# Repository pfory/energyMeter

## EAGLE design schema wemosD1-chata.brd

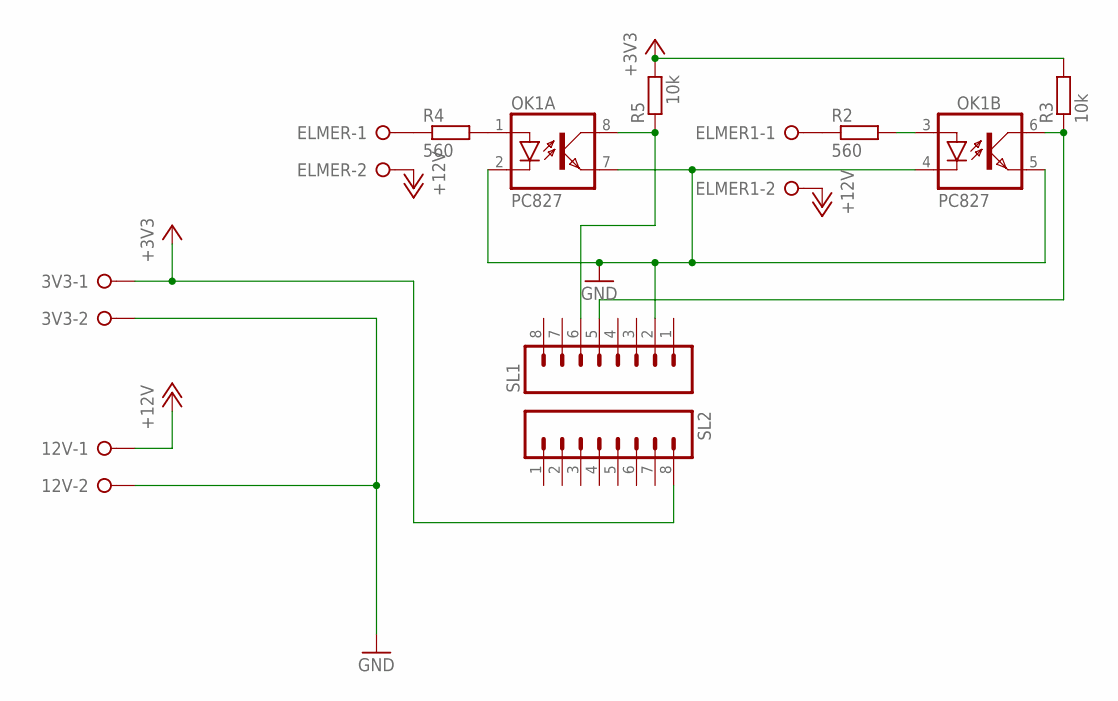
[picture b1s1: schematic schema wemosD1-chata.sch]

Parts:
3V3, 12V: W237-02P; W237-132
ELMER, ELMER1: W237-02P; W237-132
OK1: PC827; DIL08
R2, R4: 560; 0204/7
R3, R5: 10k; 0204/7
SL1, SL2: M08; 08P

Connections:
+3V3: 3V3.1, R3.2, R5.2, SL2.8
+12V: 12V.1, ELMER.2, ELMER1.2
GND: 3V3.2, 12V.2, OK1.2 (C), OK1.4 (C), OK1.5 (EMIT), OK1.7 (EMIT), SL1.2
unnamed: OK1.1 (A), R4.2
unnamed: ELMER1.1, R2.1
unnamed: OK1.3 (A), R2.2
unnamed: OK1.8 (COL), R5.1, SL1.6
unnamed: ELMER.1, R4.1
unnamed: OK1.6 (COL), R3.1, SL1.5

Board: 2 copper layers, 11 parts (0 on the bottom side), 9 nets, no tracks yet.

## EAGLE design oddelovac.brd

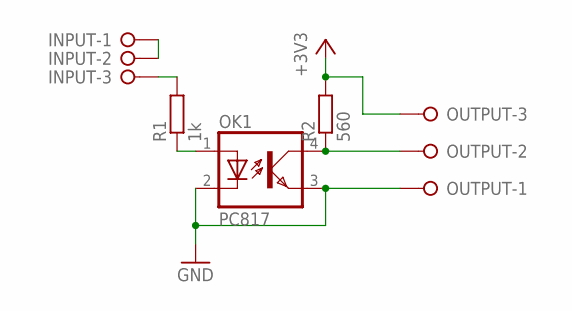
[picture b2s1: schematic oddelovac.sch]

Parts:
INPUT: W237-3E
OK1: PC817; DIL04
OUTPUT: W237-3E
R1: 1k; 0207/7
R2: 560; 0207/7

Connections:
+3V3: OUTPUT.3, R2.2
GND: OK1.2 (C), OK1.3 (EMIT), OUTPUT.1
unnamed: INPUT.3, R1.2
unnamed: OK1.1 (A), R1.1
unnamed: OK1.4 (COL), OUTPUT.2, R2.1
unnamed: INPUT.1, INPUT.2

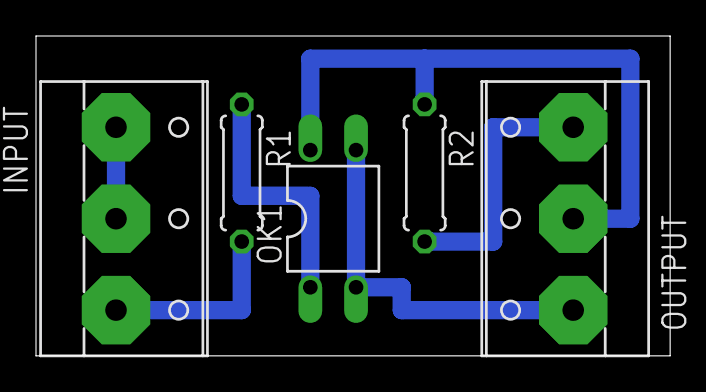
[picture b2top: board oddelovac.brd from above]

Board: 2 copper layers, 35.2 x 17.8 mm, 5 parts (0 on the bottom side), 6 nets.

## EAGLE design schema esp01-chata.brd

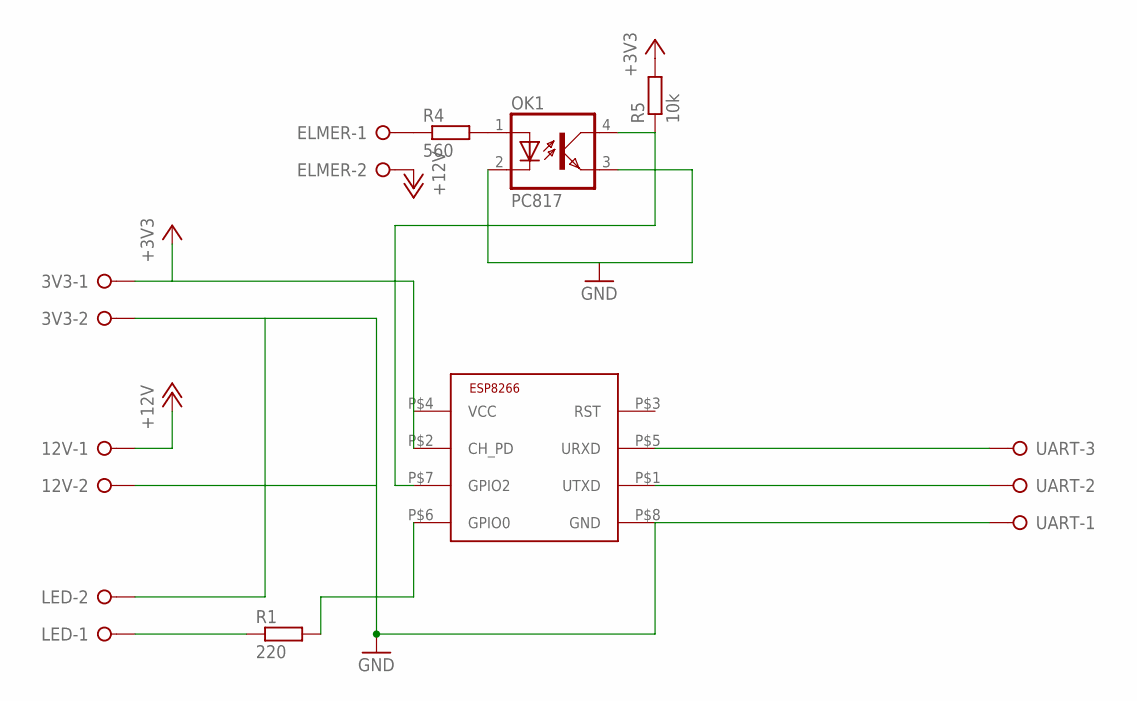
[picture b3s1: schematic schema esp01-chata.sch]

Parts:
3V3, 12V: W237-02P; W237-132
ELMER: W237-02P; W237-132
LED: W237-02P; W237-132
OK1: PC817; DIL04
R1: 220; 0204/7
R4: 560; 0204/7
R5: 10k; 0204/7
U$1: ESP8266-01; ESP-01
UART: W237-3E

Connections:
+3V3: 3V3.1, R5.2, U$1.P$2 (CH_PD), U$1.P$4 (VCC)
+12V: 12V.1, ELMER.2
GND: 3V3.2, 12V.2, LED.2, OK1.2 (C), OK1.3 (EMIT), U$1.P$8 (GND), UART.1
unnamed: LED.1, R1.1
unnamed: R1.2, U$1.P$6 (GPIO0)
unnamed: OK1.1 (A), R4.2
unnamed: U$1.P$5 (URXD), UART.3
unnamed: U$1.P$1 (UTXD), UART.2
unnamed: OK1.4 (COL), R5.1, U$1.P$7 (GPIO2)
unnamed: ELMER.1, R4.1

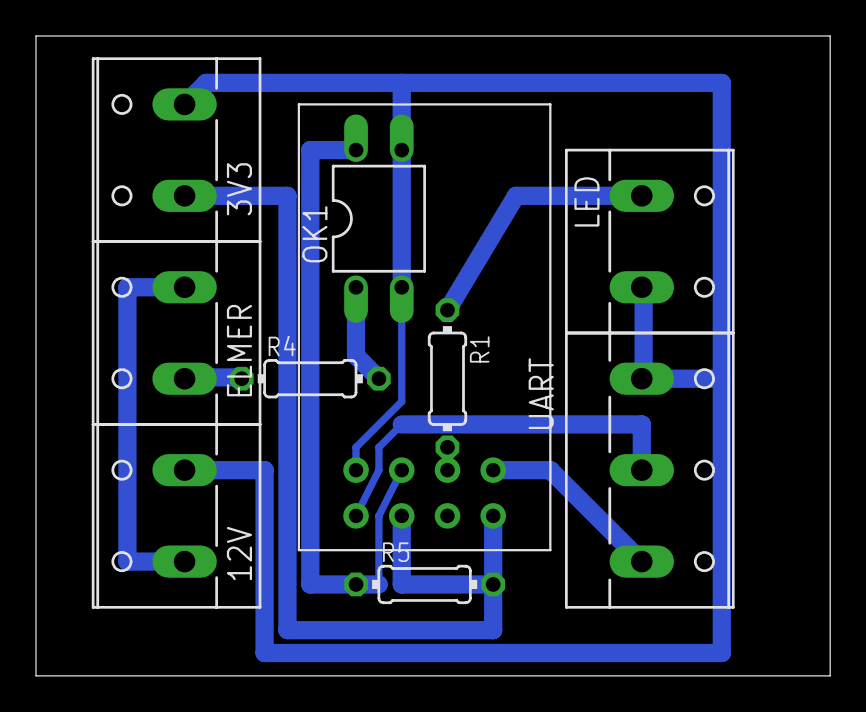
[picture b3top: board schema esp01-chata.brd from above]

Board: 2 copper layers, 44.1 x 35.5 mm, 10 parts (0 on the bottom side), 10 nets.

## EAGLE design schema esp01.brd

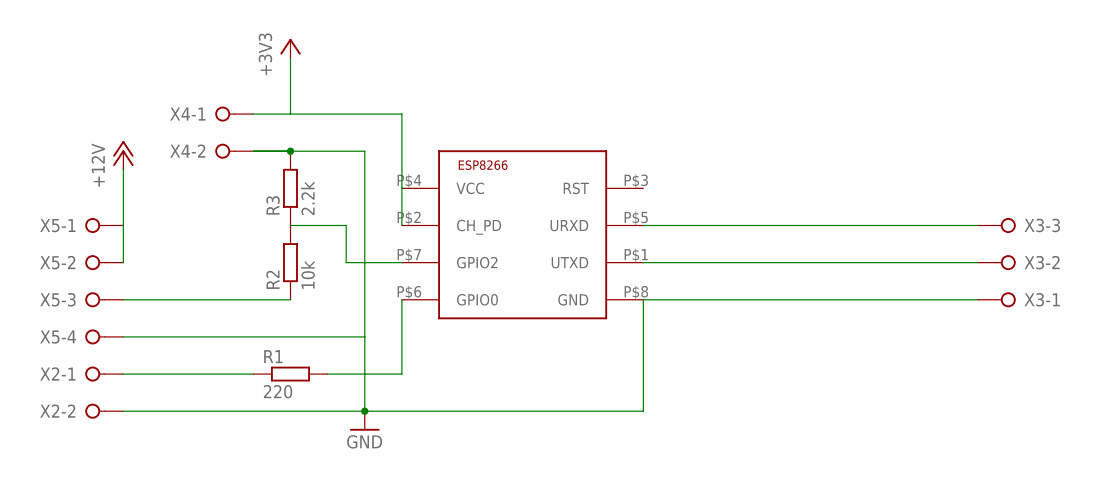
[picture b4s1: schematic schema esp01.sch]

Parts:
R1: 220; 0204/7
R2: 10k; 0204/7
R3: 2.2k; 0204/7
U$1: ESP8266-01; ESP-01
X2, X4: W237-02P; W237-132
X3: W237-3E
X5: W237-04P; W237-4P

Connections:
+3V3: U$1.P$2 (CH_PD), U$1.P$4 (VCC), X4.1
+12V: X5.1, X5.2
GND: R3.2, U$1.P$8 (GND), X2.2, X3.1, X4.2, X5.4
unnamed: R2.1, X5.3
unnamed: R1.1, X2.1
unnamed: R1.2, U$1.P$6 (GPIO0)
unnamed: U$1.P$5 (URXD), X3.3
unnamed: U$1.P$1 (UTXD), X3.2
unnamed: R2.2, R3.1, U$1.P$7 (GPIO2)

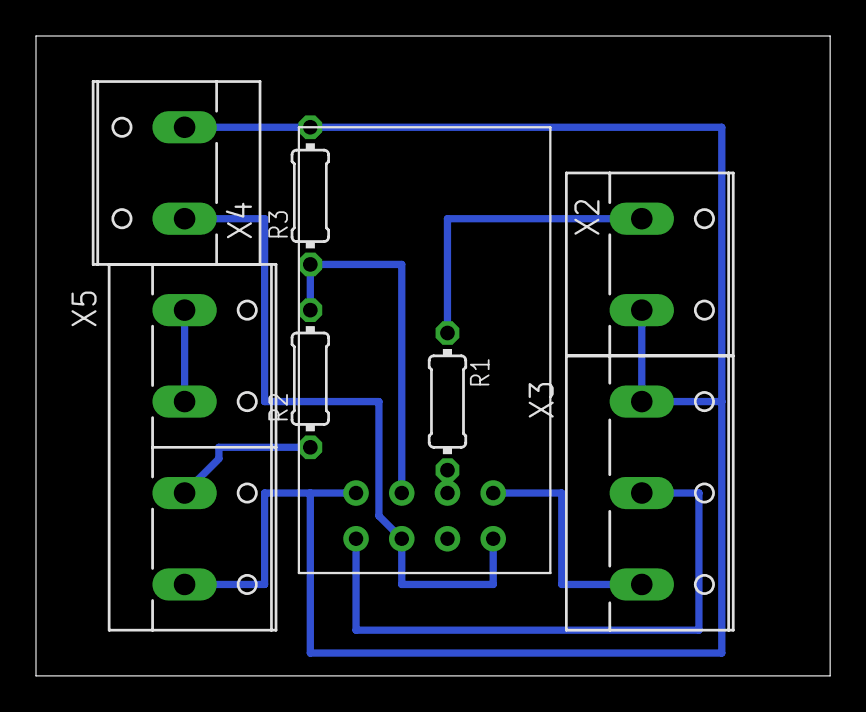
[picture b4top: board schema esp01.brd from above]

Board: 2 copper layers, 44.1 x 35.5 mm, 8 parts (0 on the bottom side), 9 nets.

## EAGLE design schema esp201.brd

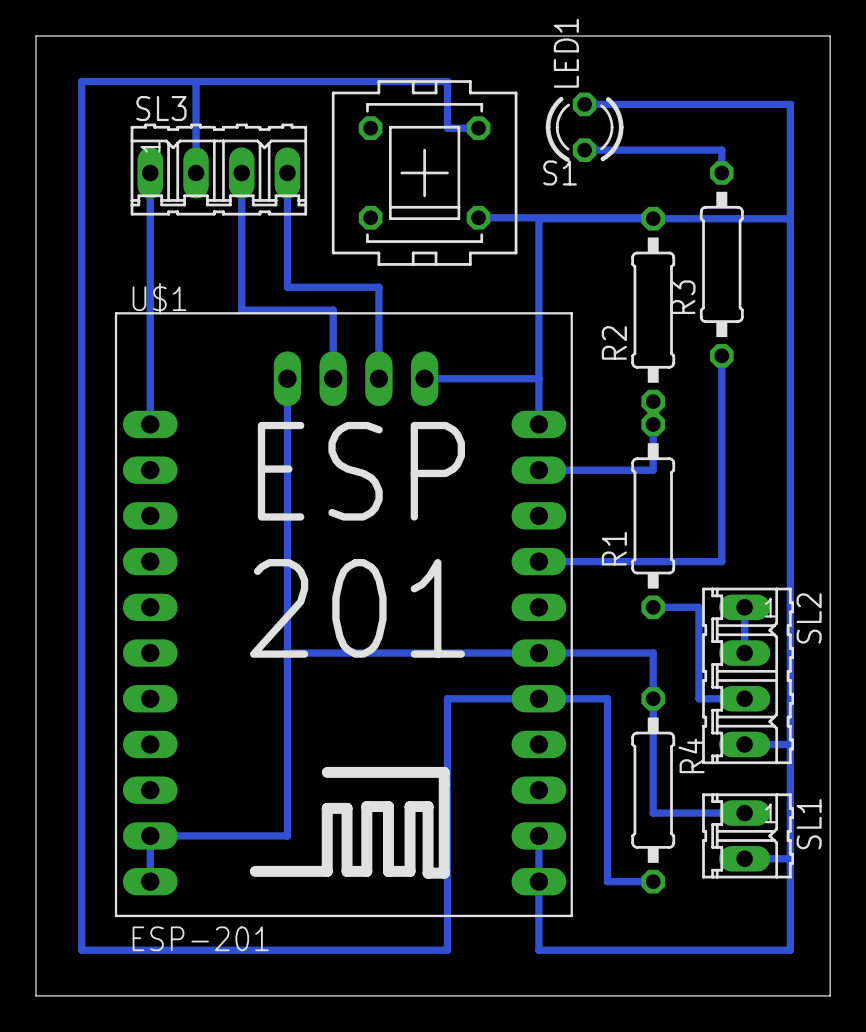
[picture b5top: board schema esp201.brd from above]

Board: 2 copper layers, 44.1 x 53.3 mm, 10 parts (0 on the bottom side), 11 nets.

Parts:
LED1: LED3MM
R1, R4: 10k; 0207/10
R2: 2k2; 0207/10
R3: 220; 0207/10
S1: PVA1R
SL1: 02P
SL2, SL3: 04P
U$1: ESP-201

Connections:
+3V3: R4.1, SL1.1, U$1.3V3, U$1.3V3_2, U$1.3V3_3, U$1.CH_PD
+12V: SL2.1, SL2.2
GND: LED1.K, R2.2, S1.4, SL1.2, SL2.4, U$1.GND, U$1.GND_2, U$1.GND_3, U$1.GPIO15
unnamed: LED1.A, R3.2
unnamed: R1.2, R2.1, U$1.GPIO13
unnamed: R3.1, U$1.GPIO14
unnamed: R4.2, S1.3, SL3.2, U$1.RST
unnamed: SL3.4, U$1.TX
unnamed: SL3.3, U$1.RX
unnamed: R1.1, SL2.3
unnamed: SL3.1, U$1.GPIO0

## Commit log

2015-12-13 init
2015-12-21 verze na cloud
2016-03-09 v0.3
2016-03-10 opravena chyba pri preteceni tmr citace
2016-03-15 +schema
2016-04-15 zmeny eagle
2016-04-20 +autoconnect
2016-04-25 +oddelovac pcb
2016-04-25 zmena pcb
2016-04-26 +bootreason
2016-04-30 v0.45 chata 30.4.2016
2016-04-30 +hodnoty resistoru
2016-05-30 +priznak pri posilani dat
2016-06-01 v0,7 elektromer doma
2016-06-01 +nodemcu
2016-06-03 v0,70 - ulozeni stavu do EEPROM
2016-07-04 +fw 1.5.1
2016-07-04 +modules
2016-07-04 v0,7 na lua 151 4.7.2016 na chatu
2016-07-04 v0,7 lua151 4.7.2016
2016-07-27 pi na chate
2016-11-06 uprava doma
2016-12-13 +ino
2016-12-14 ukladani do pameti
2016-12-15 zapis stavu do souboru
2017-01-09 +reset +nastaveni poctu pulzu
2017-01-10 rozsliseni boot reason
2017-01-11 webserver volitelne HB a verze v pevnem intervalu
2017-01-12 zapisovani podrobneho reset info do mqtt pri startu
2019-05-09 inot
2020-06-02 upravy na novejsi styl
2020-07-03 + ota
2021-04-12 opravena chyba s prerusenim
2021-04-13 0,91
2021-08-10 0.72
2021-12-07 0.40
2021-12-07 1.00
2021-12-12 1.01
2021-12-12 0.41
2021-12-12 1.02
2026-03-19 předěláno na Tasmota
2026-03-24 tasmotized
